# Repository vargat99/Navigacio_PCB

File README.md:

# KAPCSRAJZON
## Motor control: pipa
## Sensors
	GPS: pipa
	IMU: kéne egy level shifter és egy 1.8V táp
## Power management
	ShengYang datasheet ennyit tudott
## MCU Logic
	GPS, földek be van kötve
	kijövő táp logikai 3.3V, 5V be van kötve
	MCU bemenő táp be van kötve
	
## Kell még
	motor_mode
	motor ki/be kapcsolás
	enkóderek
	pwm vezérlés

	sensorok I2C, SPI ...

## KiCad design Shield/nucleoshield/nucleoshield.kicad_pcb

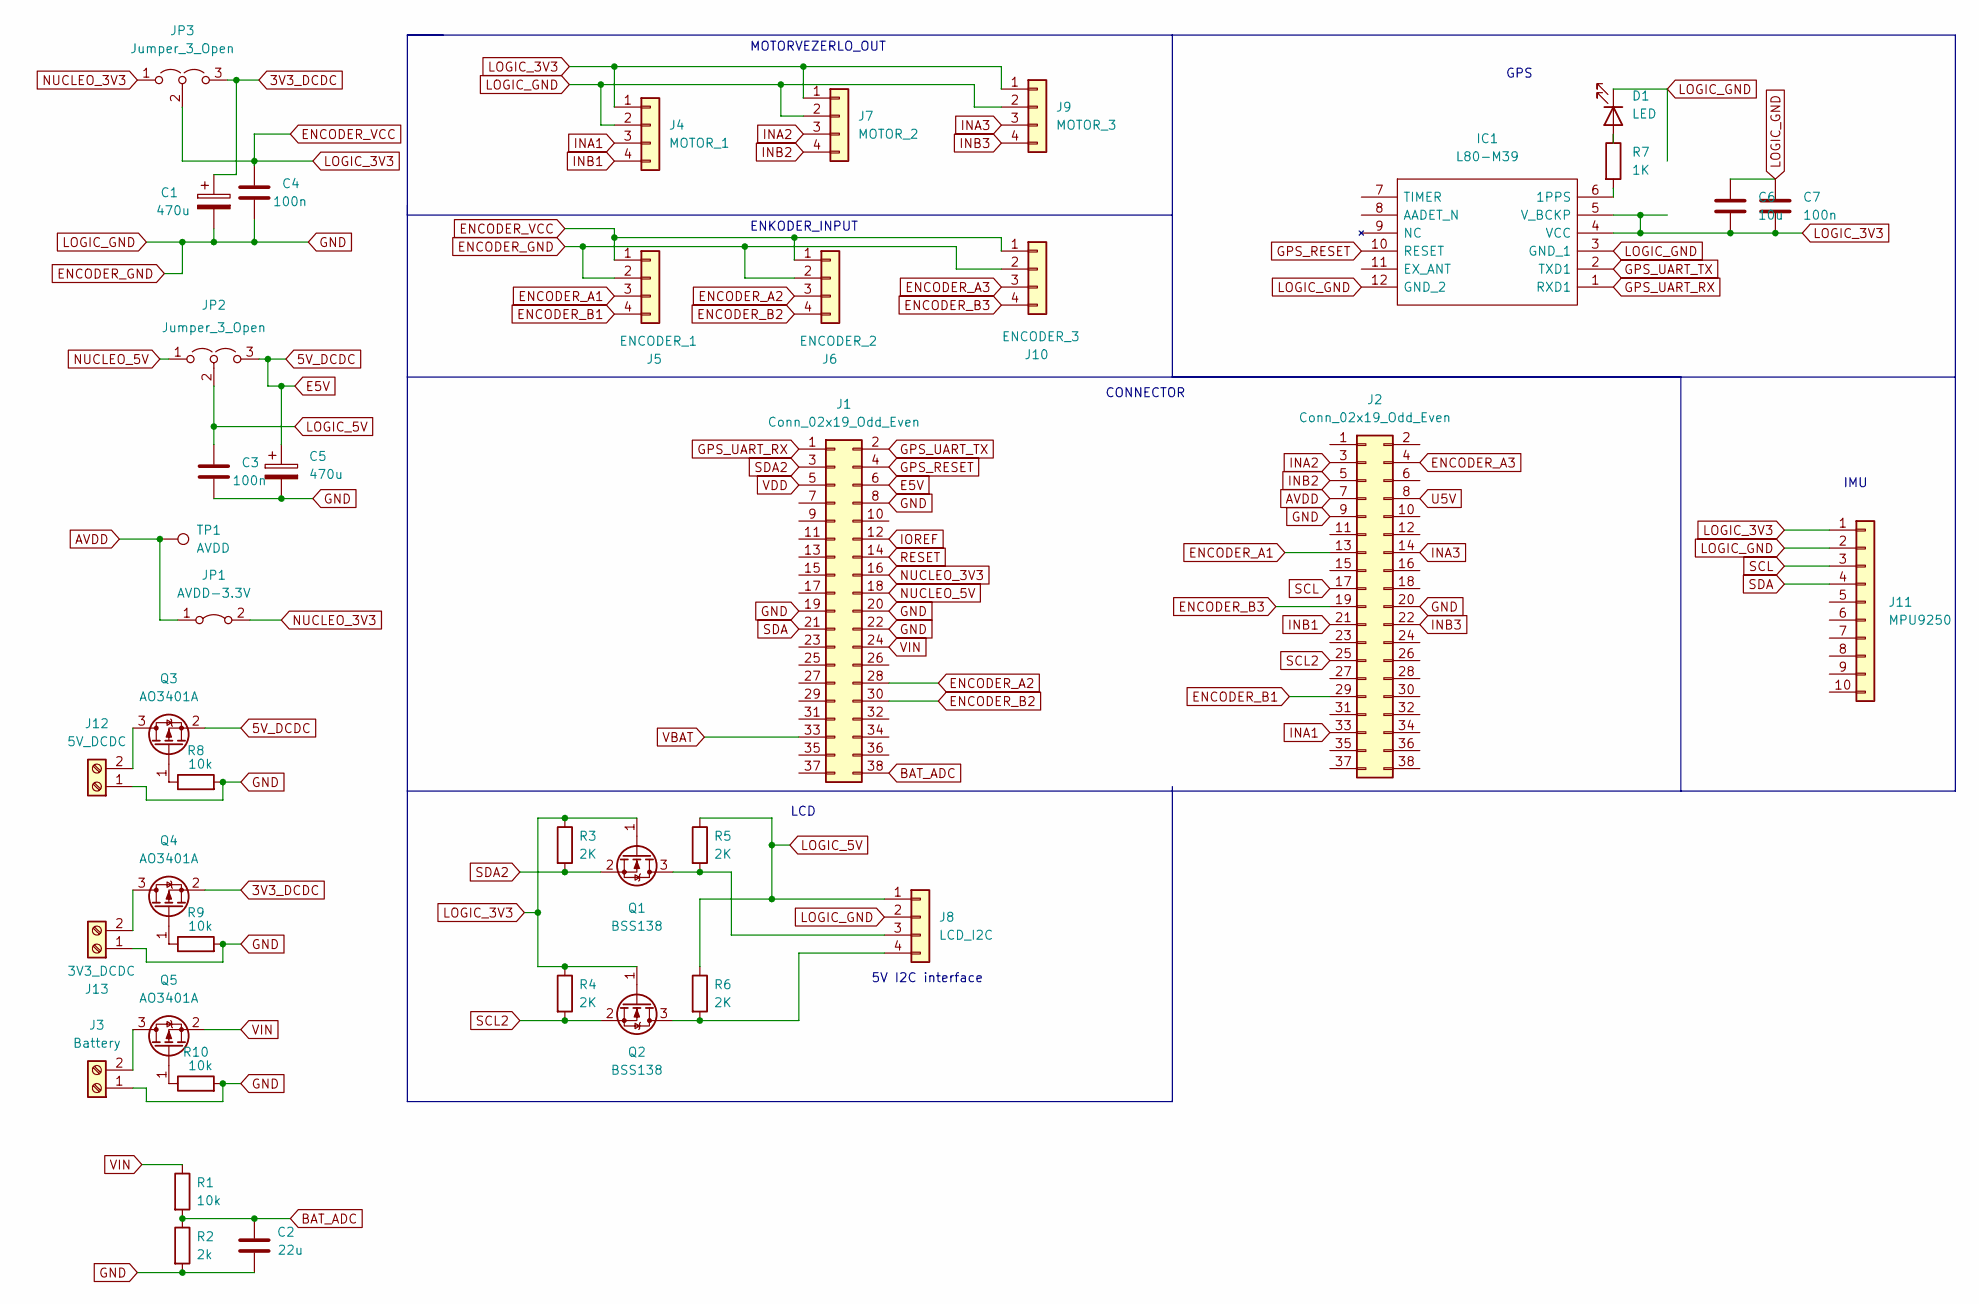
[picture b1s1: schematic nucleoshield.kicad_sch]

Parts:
C1, C5: 470u; CP_Radial_D8.0mm_P3.50mm
C2: 22u; C_1206_3216Metric
C3, C4, C7: 100n; C_1206_3216Metric
C6: 10u; C_1206_3216Metric
D1: LED; LED_0805_2012Metric
IC1: L80-M39; Manufacturer_Part_Number L80-M39; Mouser Part Number 277-L80-M39
J1, J2: Conn_02x19_Odd_Even; PinSocket_2x19_P2.54mm_Vertical
J3: Battery; TerminalBlock_Altech_AK300-2_P5.00mm
J4: MOTOR_1; JST_EH_B4B-EH-A_1x04_P2.50mm_Vertical
J5: ENCODER_1; JST_EH_B4B-EH-A_1x04_P2.50mm_Vertical
J6: ENCODER_2; JST_EH_B4B-EH-A_1x04_P2.50mm_Vertical
J7: MOTOR_2; JST_EH_B4B-EH-A_1x04_P2.50mm_Vertical
J8: LCD_I2C; JST_EH_B4B-EH-A_1x04_P2.50mm_Vertical
J9: MOTOR_3; JST_EH_B4B-EH-A_1x04_P2.50mm_Vertical
J10: ENCODER_3; JST_EH_B4B-EH-A_1x04_P2.50mm_Vertical
J11: MPU9250; PinHeader_1x10_P2.54mm_Vertical
J12: 5V_DCDC; TerminalBlock_Altech_AK300-2_P5.00mm
J13: 3V3_DCDC; TerminalBlock_Altech_AK300-2_P5.00mm
JP1: AVDD-3.3V; SolderJumper-2_P1.3mm_Bridged2Bar_Pad1.0x1.5mm
JP2, JP3: Jumper_3_Open; PinHeader_1x03_P2.54mm_Vertical
Q1, Q2: BSS138; SOT-23
Q3, Q4, Q5: AO3401A; SOT-23
R1, R8, R9, R10: 10k; R_0805_2012Metric
R2: 2k; R_0805_2012Metric
R3, R4, R5, R6: 2K; R_0805_2012Metric
R7: 1K; R_0805_2012Metric
TP1: AVDD; TestPoint_THTPad_1.0x1.0mm_Drill0.5mm

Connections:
3V3_DCDC: C1.1, JP3.3 (B), Q4.2 (S)
5V_DCDC: C5.1, J1.6, JP2.3 (B), Q3.2 (S)
AVDD: J2.7, JP1.1 (A), TP1.1
BAT_ADC: C2.2, J1.38, R1.2, R2.1
ENCODER_A1: J2.13, J5.3
ENCODER_A2: J1.28, J6.3
ENCODER_A3: J2.4, J10.3
ENCODER_B1: J2.29, J5.4
ENCODER_B2: J1.30, J6.4
ENCODER_B3: J2.19, J10.4
ENCODER_GND: C1.2, C2.1, C3.2, C4.2, C5.2, C6.1, C7.1, D1.1 (K), IC1.3 (GND_1), IC1.12 (GND_2), J1.8, J1.19, J1.20, J1.22, J2.9, J2.20, J3.1, J4.2, J5.2, J6.2, J7.2, J8.2, J9.2, J10.2, J11.2, J12.1, J13.1, R2.2, R8.2, R9.2, R10.2
ENCODER_VCC: C4.1, C6.2, C7.2, IC1.4 (VCC), IC1.5 (V_BCKP), J4.1, J5.1, J6.1, J7.1, J9.1, J10.1, J11.1, JP3.2 (C), Q1.1 (G), Q2.1 (G), R3.1, R4.1
GPS_RESET: IC1.10 (RESET), J1.4
GPS_UART_RX: IC1.1 (RXD1), J1.1
GPS_UART_TX: IC1.2 (TXD1), J1.2
INA1: J2.33, J4.3
INA2: J2.3, J7.3
INA3: J2.14, J9.3
INB1: J2.21, J4.4
INB2: J2.5, J7.4
INB3: J2.22, J9.4
IOREF: J1.12
LOGIC_5V: C3.1, J8.1, JP2.2 (C), R5.1, R6.1
NUCLEO_3V3: J1.16, JP1.2 (B), JP3.1 (A)
NUCLEO_5V: J1.18, JP2.1 (A)
unnamed: D1.2 (A), R7.1
unnamed: IC1.6 (1PPS), R7.2
unnamed: J3.2, Q5.3 (D)
unnamed: J8.3, Q1.3 (D), R5.2
unnamed: J8.4, Q2.3 (D), R6.2
unnamed: J12.2, Q3.3 (D)
unnamed: J13.2, Q4.3 (D)
unnamed: Q3.1 (G), R8.1
unnamed: Q4.1 (G), R9.1
unnamed: Q5.1 (G), R10.1
RESET: J1.14
SCL: J2.17, J11.3
SCL2: J2.25, Q2.2 (S), R4.2
SDA: J1.21, J11.4
SDA2: J1.3, Q1.2 (S), R3.2
U5V: J2.8
VBAT: J1.33
VDD: J1.5
VIN: J1.24, Q5.2 (S), R1.1

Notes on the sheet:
IMU
CONNECTOR
ENKODER_INPUT
5V I2C interface
LCD
GPS
MOTORVEZERLO_OUT

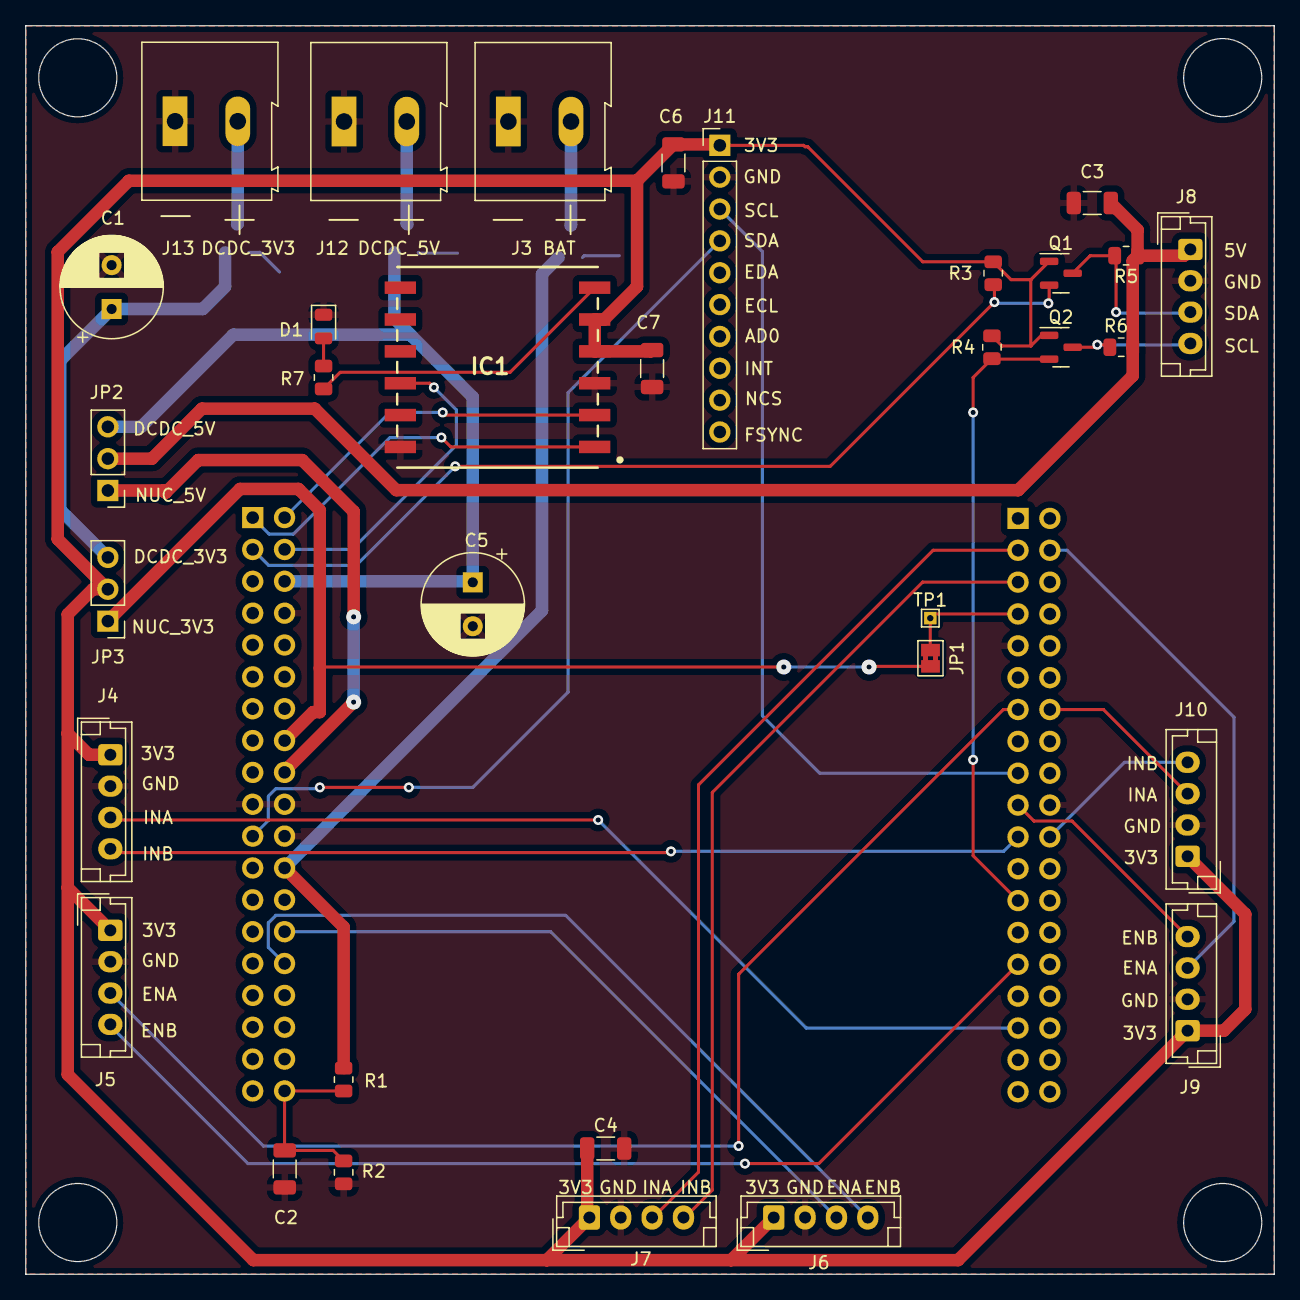
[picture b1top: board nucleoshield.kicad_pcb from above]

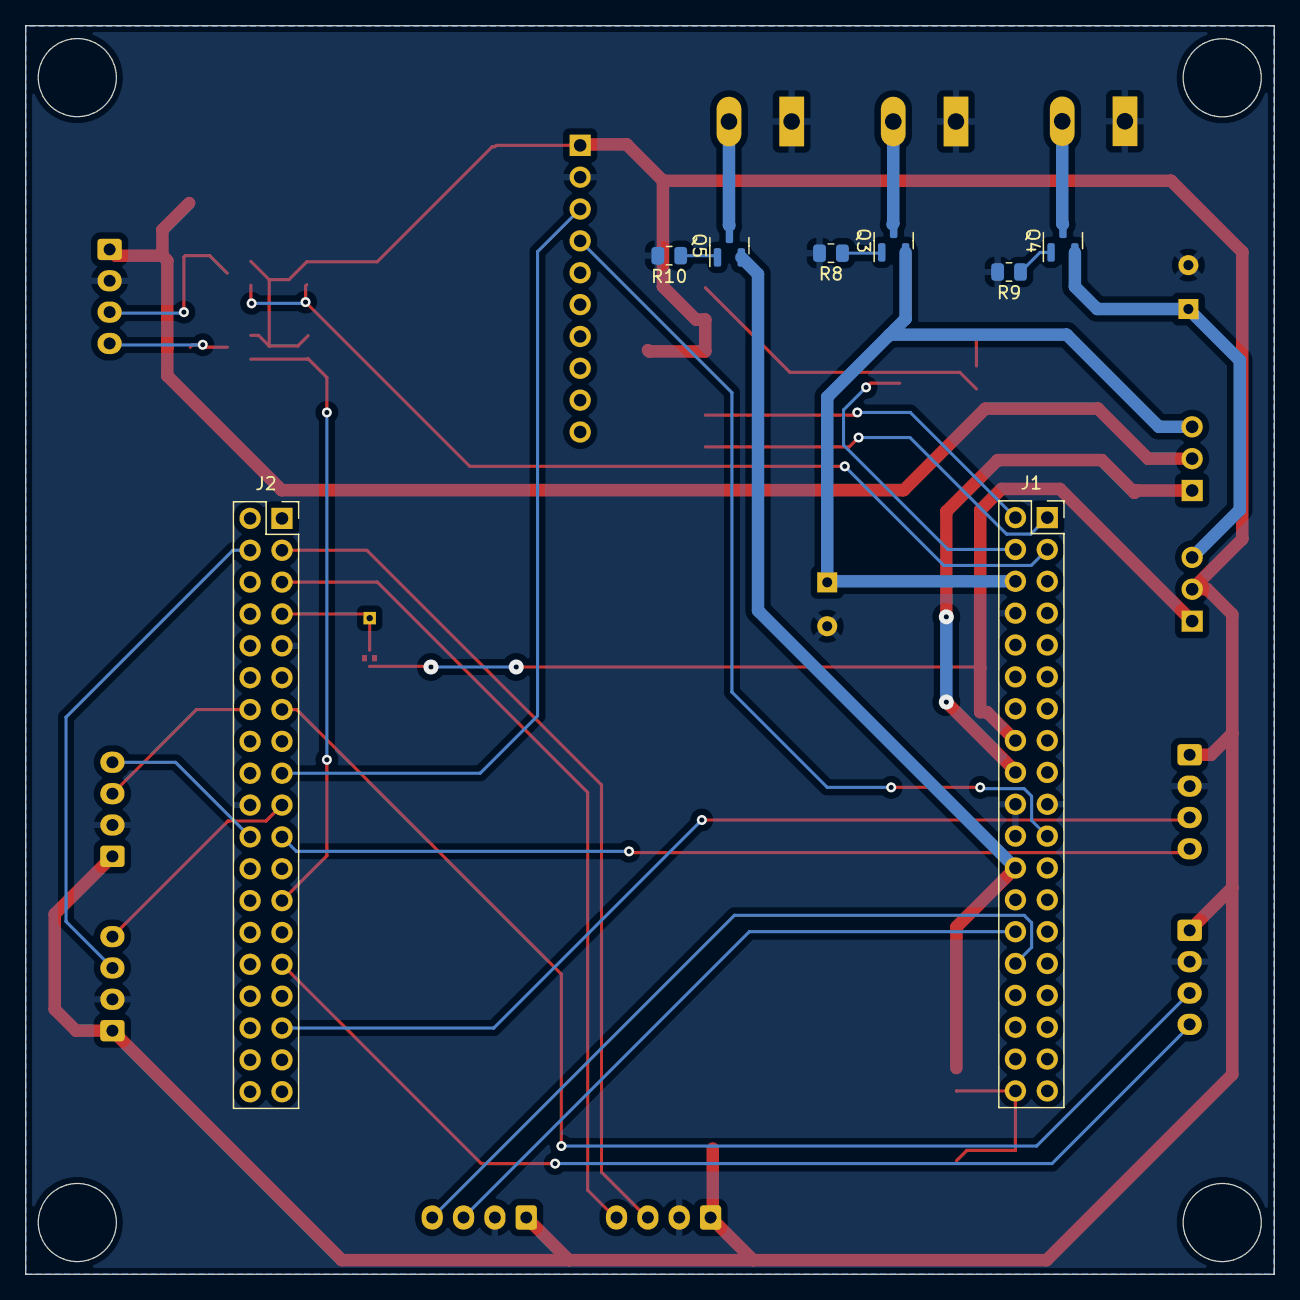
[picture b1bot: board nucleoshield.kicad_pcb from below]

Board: 2 copper layers, 99.6 x 99.6 mm, 41 parts (8 on the bottom side), 39 nets.

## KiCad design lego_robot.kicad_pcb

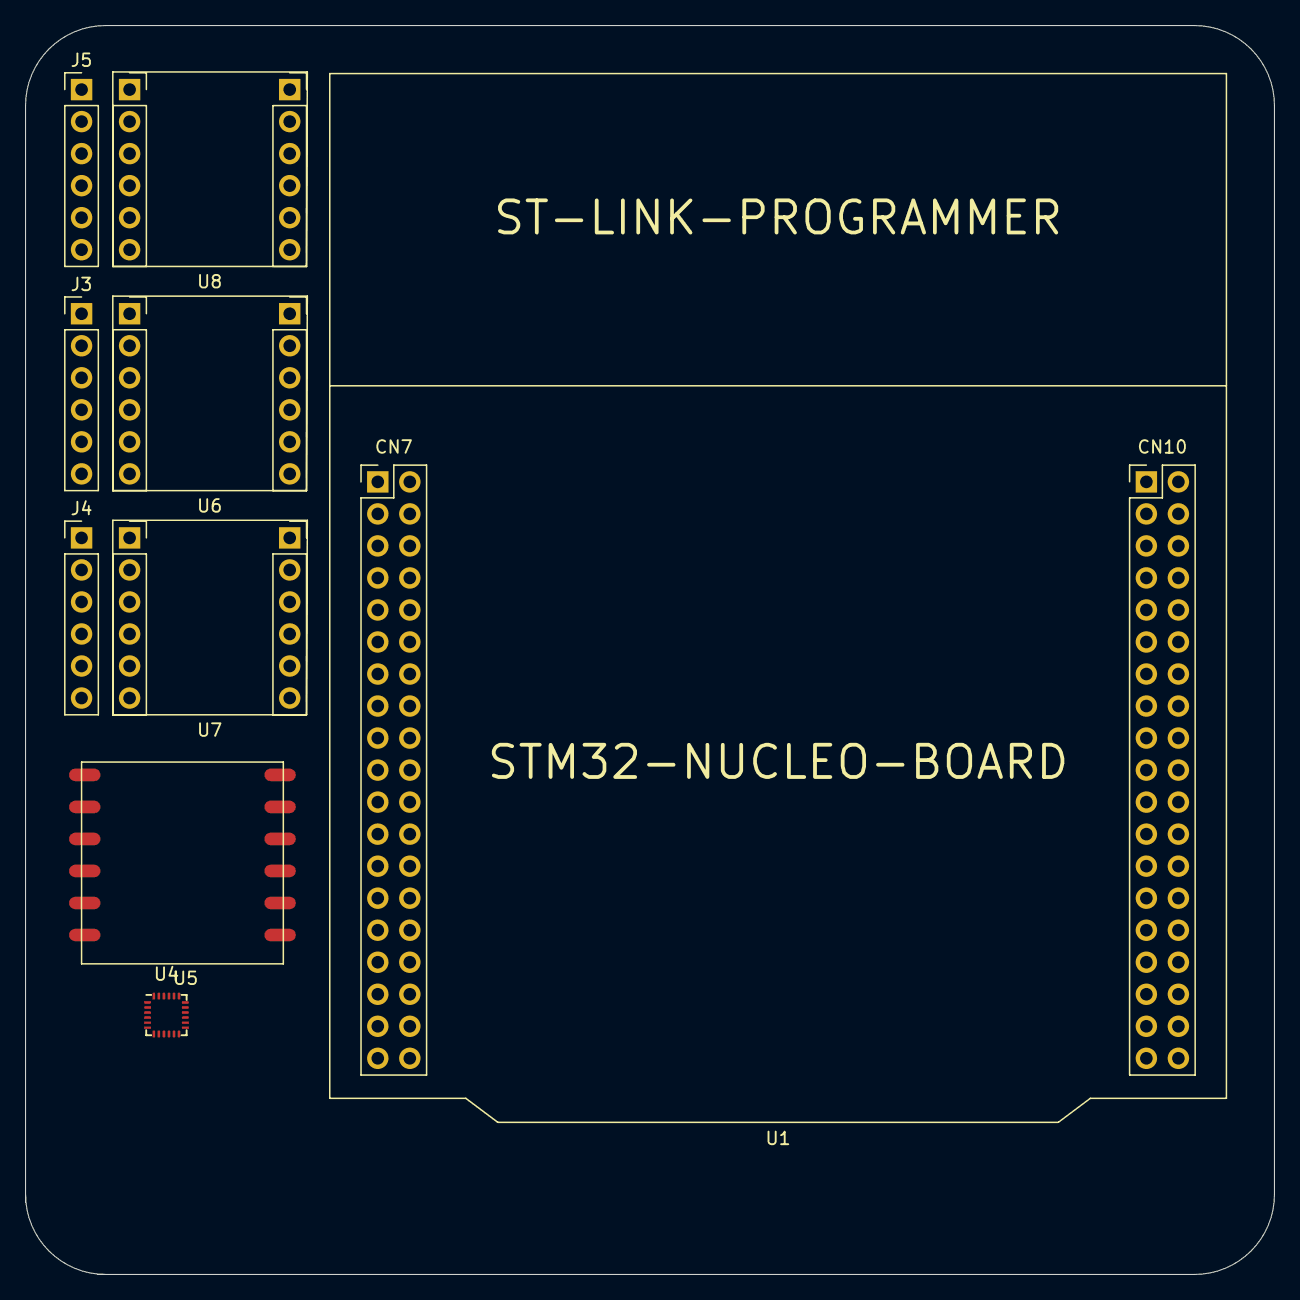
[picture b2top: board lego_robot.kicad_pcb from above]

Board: 2 copper layers, 99.1 x 99.1 mm, 9 parts (0 on the bottom side), 17 nets, no tracks yet.

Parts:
J3, J4, J5: Motor_Connector; PinHeader_1x06_P2.54mm_Vertical
U1: STM32-NUCLEO-F446RE; ST_NUCLEO64
U4: ICM-20948; InvenSense_QFN-24_3x3mm_P0.4mm
U5: L80-M39
U6, U7, U8: BD65496MUV

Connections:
/GPS_RESET: U1.3, U5.10
/GPS_UART_RX: U1.1, U5.1
/GPS_UART_TX: U1.2, U5.2
/LOGIC_3V3: J3.4, J4.4, J5.4, U1.16, U4.8, U4.13, U5.4, U5.5, U6.1, U7.1, U8.1
/LOGIC_GND: J3.3, J4.3, J5.3, U1.8, U1.19, U1.20, U1.22, U1.47, U1.58, U1.70, U5.3, U5.12, U6.6, U7.6, U8.6
/MOTOR1_A: J3.1, U6.3
/MOTOR1_B: J3.2, U6.4
/MOTOR2_A: J4.1, U7.3
/MOTOR2_B: J4.2, U7.4
/MOTOR3_A: J5.1, U8.3
/MOTOR3_B: J5.2, U8.4
/MOTOR_GND: U6.2, U7.2, U8.2
/MOTOR_MODE: U6.12, U7.12, U8.12
/MOTOR_TR1: U6.8, U7.8, U8.8
/MOTOR_TR2: U6.9, U7.9, U8.9
/MOTOR_VIN: U6.5, U7.5, U8.5
GND: U4.18, U4.20

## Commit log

2021-11-29 init commit
2021-11-29 Add README
2022-01-23 More work on schematic
2022-01-23 Preliminary PCB edge cuts and placements
2022-02-02 Add lego_robot_kapcsrajz.pdf
2022-04-12 mostly done
2022-08-15 Nucleo shield
2022-08-25 Schematic and pcb ready
2022-08-27 power modifications
2022-08-30 Power connector
2022-08-31 pdfs
2022-08-31 small changes
2022-09-06 Csatlakozók megváltoztatva, polaritásvédelem, apróbb javítások
2022-09-16 Fetek kicserélve
2022-09-25 Enkóderek timer bemenetekhez rendelve
2022-10-09 DRC update
2023-12-13 fixes
2023-12-13 Schematic update
